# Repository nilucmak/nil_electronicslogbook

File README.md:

# 🌊 PRU Robotics – Electronics & Underwater Systems Logbook
Welcome to my personal development repository focusing on **Underwater Robotics**, **Electronics**, and **PCB Design**.  
This repo documents my learning journey and project progress as a member of the **PRU Robotics – Underwater Systems Team**.

## 🧭 About Me
🎓 Electrical & Electronics Engineering student at **Piri Reis University**  
🤖 Member of **PRU Robotics Team – Underwater Systems (ROV & AUV)**  
⚡ Interests: Embedded Systems, PCB Design, Sensor Integration, Control Systems, and Autonomous Robotics  

### ⚙️ Repository Structure
PCB_Designs/ → My custom PCB boards (motor drivers, power modules, sensor interfaces)
ROV_Projects/ → Designs and control systems for ROV & AUV
Embedded_Systems/ → Arduino, STM32 and Raspberry Pi projects
Notes_and_Resources/ → Theory notes, references, research papers
Experiments/ → Prototype circuits and test setups

####🌐 Focus Areas
- **ROV (Remotely Operated Vehicle):** Control systems, thruster management, camera integration  
- **AUV (Autonomous Underwater Vehicle):** Navigation, sensor fusion, mission automation  
- **PCB Design:** Power distribution boards, motor control boards, signal conditioning circuits  
- **Embedded Systems:** Microcontroller programming, sensor interfacing, data acquisition

#####📚 Current Learning Plan
- [ ] Master KiCad / Altium for multi-layer PCB design  
- [ ] Develop a motor control PCB for ROV thrusters  
- [ ] Interface IMU and pressure sensors with STM32  
- [ ] Implement PID control for underwater stability  
- [ ] Study ROS integration for autonomous underwater missions  
  
*This repository represents my continuous learning journey in electronics and underwater robotics.*

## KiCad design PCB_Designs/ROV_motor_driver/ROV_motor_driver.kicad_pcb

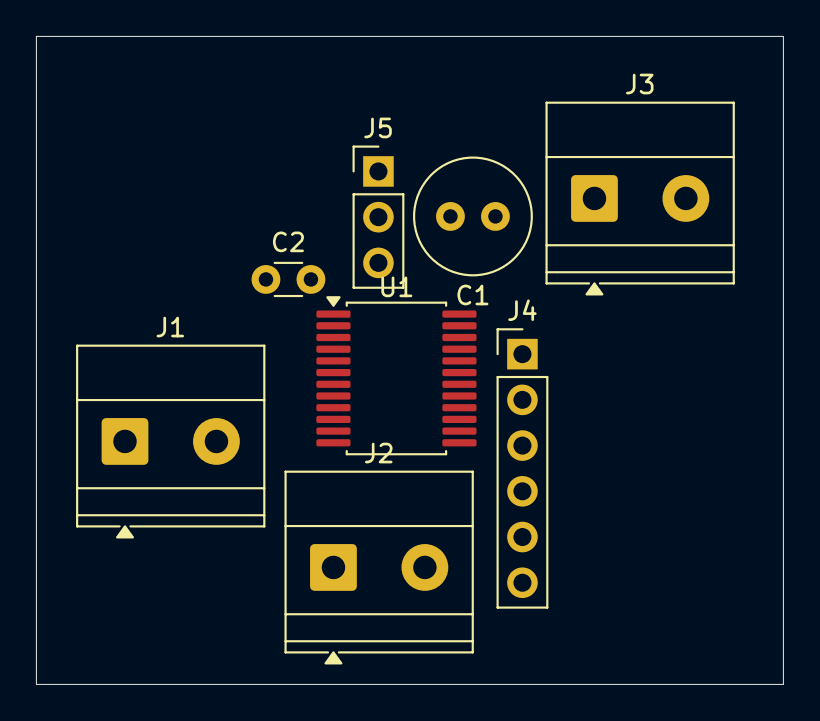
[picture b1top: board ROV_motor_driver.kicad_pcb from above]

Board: 2 copper layers, 41.5 x 36.0 mm, 8 parts (0 on the bottom side), 13 nets, no tracks yet.

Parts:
C1: 10uF; C_Radial_D6.3mm_H7.0mm_P2.50mm
C2: 0.1uF; C_Disc_D3.0mm_W1.6mm_P2.50mm
J1, J2, J3: Conn_01x02_Pin; TerminalBlock_Phoenix_MKDS-1,5-2-5.08_1x02_P5.08mm_Horizont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
J4: Conn_01x06_Pin; PinHeader_1x06_P2.54mm_Vertical
J5: Conn_01x03_Pin; PinHeader_1x03_P2.54mm_Vertical
U1: TB6612FNG; SSOP-24_5.3x8.2mm_P0.65mm

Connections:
GND: C1.2, C2.2, J3.2, J5.2, U1.3 (PGND1), U1.4 (PGND1), U1.9 (PGND2), U1.10 (PGND2), U1.18 (GND)
unnamed: J1.1, U1.1 (AO1), U1.2 (AO1)
unnamed: J2.1, U1.11 (BO1), U1.12 (BO1)
unnamed: J2.2, U1.7 (BO2), U1.8 (BO2)
unnamed: C1.1, J3.1, U1.13 (VM2), U1.14 (VM3), U1.24 (VM1)
unnamed: J4.1, U1.23 (PWMA)
unnamed: J4.2, U1.21 (AIN1)
unnamed: J4.3, U1.22 (AIN2)
unnamed: J4.4, U1.15 (PWMB)
unnamed: J4.5, U1.17 (BIN1)
unnamed: J4.6, U1.16 (BIN2)
unnamed: C2.1, J5.1, U1.19 (STBY), U1.20 (VCC)
unnamed: U1.5 (AO2), U1.6 (AO2)

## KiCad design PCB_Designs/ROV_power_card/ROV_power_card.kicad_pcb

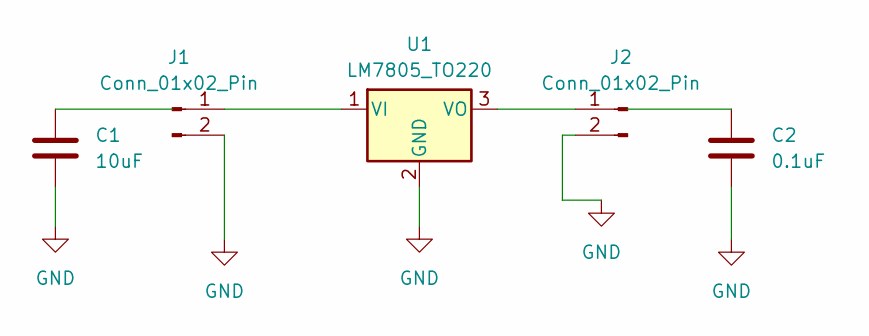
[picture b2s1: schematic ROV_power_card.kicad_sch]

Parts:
C1: 10uF; CP_Radial_D5.0mm_P2.50mm
C2: 0.1uF; C_Disc_D3.0mm_W1.6mm_P2.50mm
J1, J2: Conn_01x02_Pin; PinHeader_1x02_P2.54mm_Vertical
U1: LM7805_TO220; TO-220-3_Vertical

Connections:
GND: C1.2, C2.2, J1.2, J2.2, U1.2 (GND)
unnamed: J1.1, U1.1 (VI)
unnamed: J2.1, U1.3 (VO)

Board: 2 copper layers, 5 parts (0 on the bottom side), 3 nets, no tracks yet.

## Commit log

2025-10-26 Create README.md
    Added README with repository description and learning plan
2025-10-28 LM7805 Voltaj Regulator Card
    Day 2, LM7805 Voltaj Regulator Card (KiCad Project)
2025-10-28 Motor Driver Card
    Day 3, Motor driver card project for ROV's (KiCad project)
